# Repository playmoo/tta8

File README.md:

# tta8
8bit Transport Triggered Processor

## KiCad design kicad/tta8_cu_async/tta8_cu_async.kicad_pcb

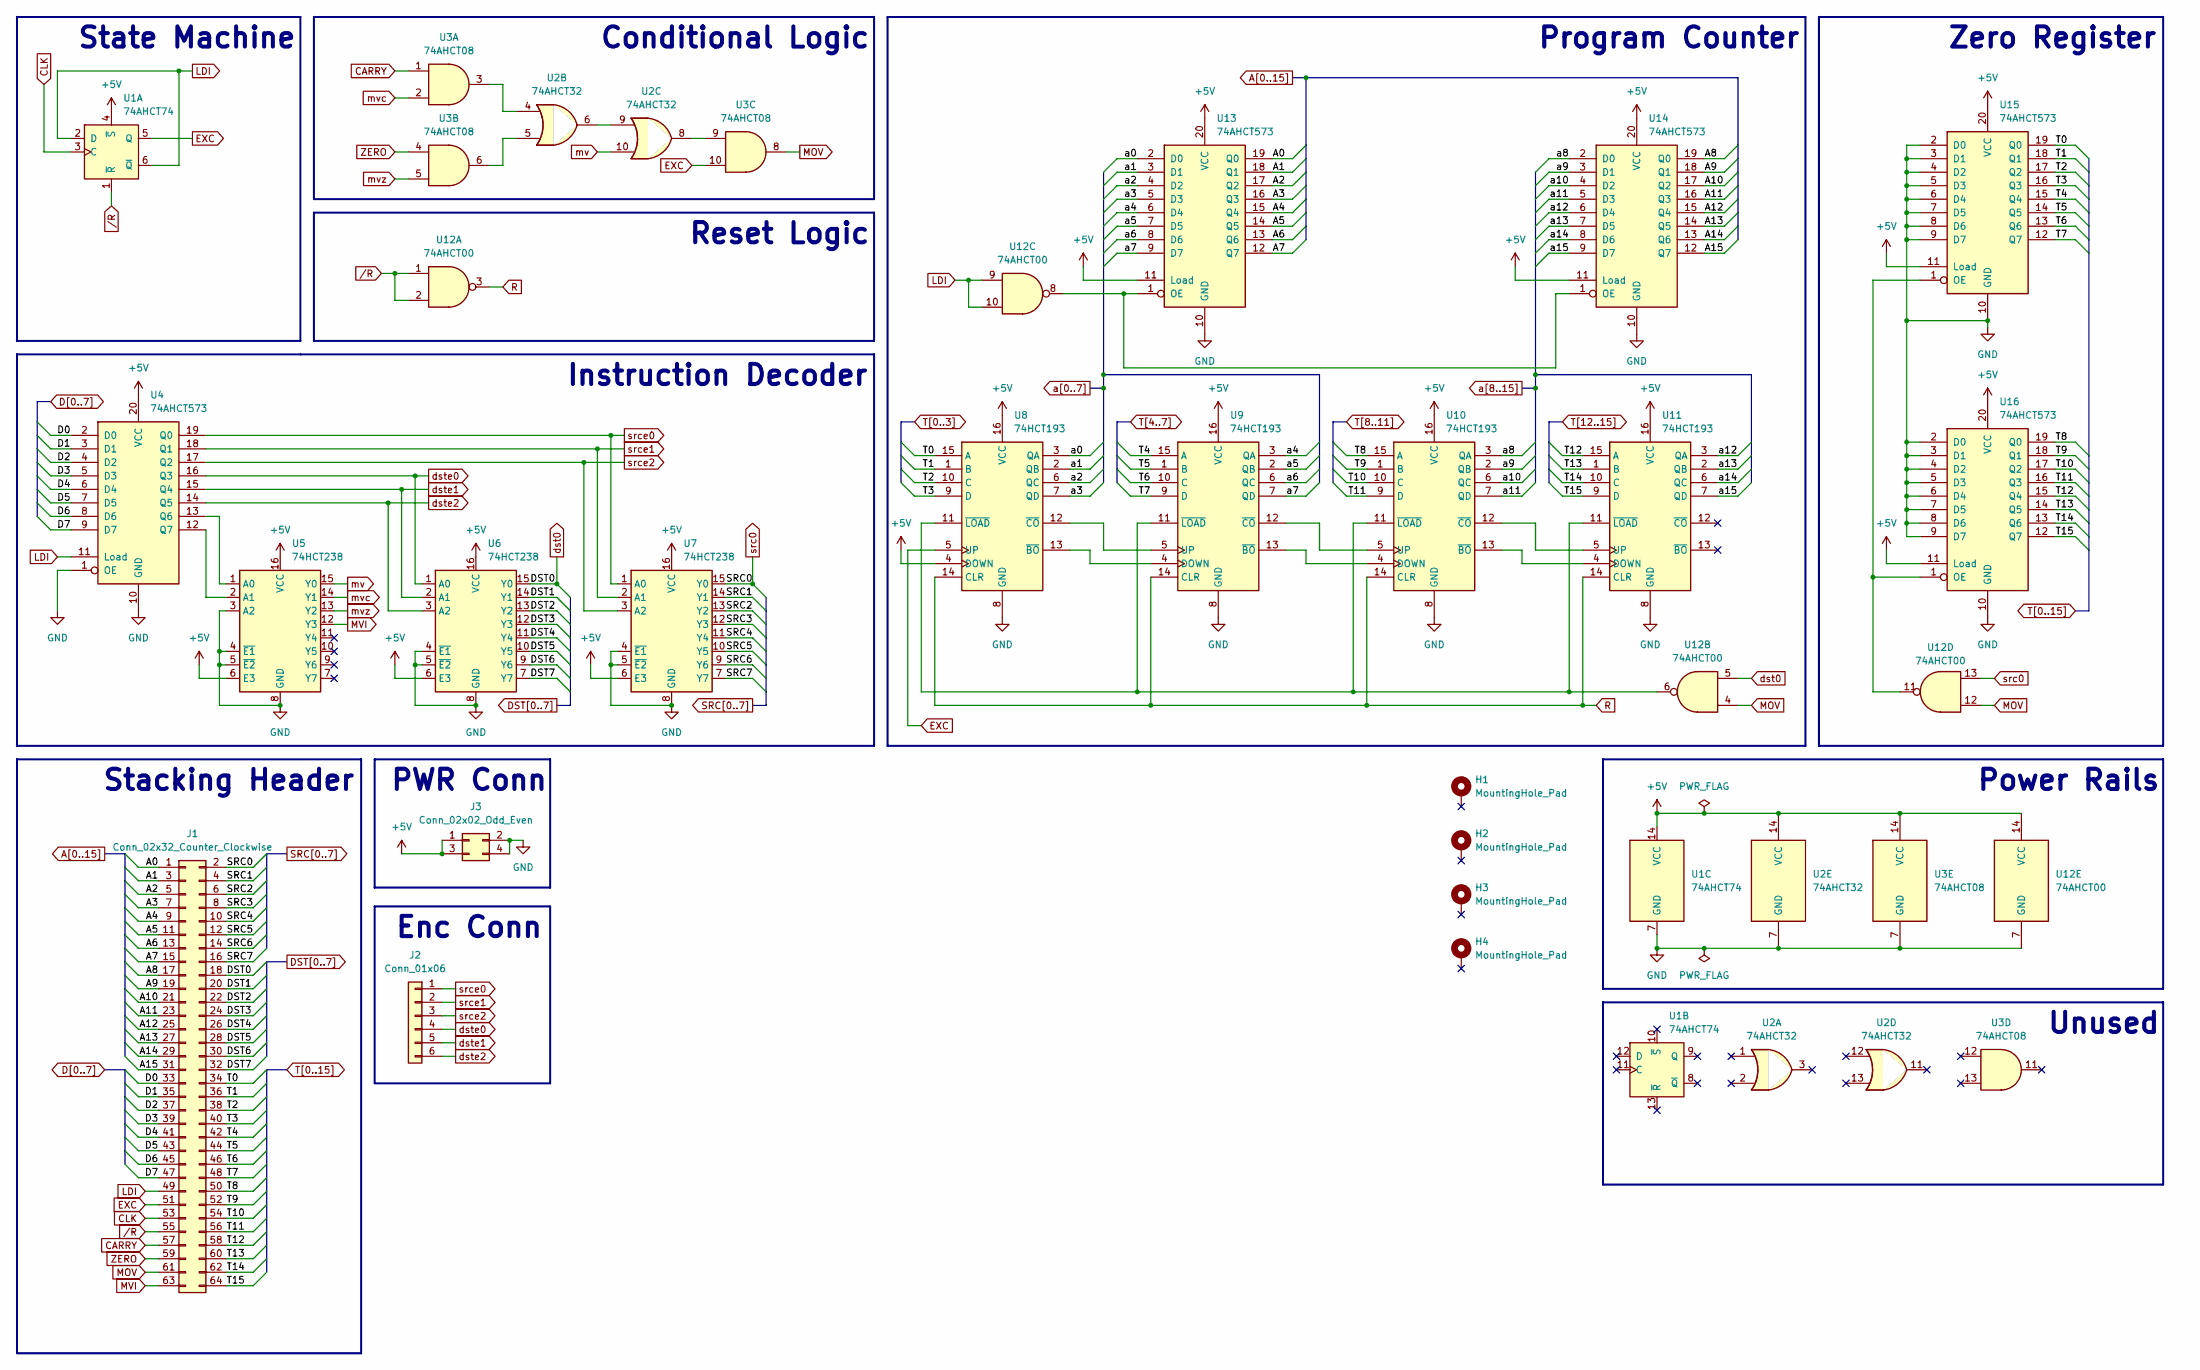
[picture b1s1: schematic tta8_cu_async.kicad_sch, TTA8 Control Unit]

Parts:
H1, H2, H3, H4: MountingHole_Pad; MountingHole_3.2mm_M3_Pad
J1: Conn_02x32_Counter_Clockwise; PinHeader_2x32_P2.54mm_Vertical
J2: Conn_01x06; PinSocket_1x06_P2.54mm_Vertical
J3: Conn_02x02_Odd_Even; Molex_Micro-Fit_3.0_43045-0400_2x02_P3.00mm_Horizontal
U1: 74AHCT74; DIP-14_W7.62mm_Socket
U2: 74AHCT32; DIP-14_W7.62mm_Socket
U3: 74AHCT08; DIP-14_W7.62mm_Socket
U4, U13, U14, U15, U16: 74AHCT573; DIP-20_W7.62mm_Socket
U5, U6, U7: 74HCT238; DIP-16_W7.62mm_Socket
U8, U9, U10, U11: 74HCT193; DIP-16_W7.62mm_Socket
U12: 74AHCT00; DIP-14_W7.62mm_Socket

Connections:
+5V: J3.1, J3.3, U1.4 (~S), U1.14 (VCC), U2.14 (VCC), U3.14 (VCC), U4.20 (VCC), U5.6 (E3), U5.16 (VCC), U6.6 (E3), U6.16 (VCC), U7.6 (E3), U7.16 (VCC), U8.4 (DOWN), U8.16 (VCC), U9.16 (VCC), U10.16 (VCC), U11.16 (VCC), U12.14 (VCC), U13.11 (Load), U13.20 (VCC), U14.11 (Load), U14.20 (VCC), U15.11 (Load), U15.20 (VCC), U16.11 (Load), U16.20 (VCC)
A0: J1.1, U13.19 (Q0)
A1: J1.3, U13.18 (Q1)
A2: J1.5, U13.17 (Q2)
A3: J1.7, U13.16 (Q3)
A4: J1.9, U13.15 (Q4)
A5: J1.11, U13.14 (Q5)
A6: J1.13, U13.13 (Q6)
A7: J1.15, U13.12 (Q7)
A8: J1.17, U14.19 (Q0)
A9: J1.19, U14.18 (Q1)
A10: J1.21, U14.17 (Q2)
A11: J1.23, U14.16 (Q3)
A12: J1.25, U14.15 (Q4)
A13: J1.27, U14.14 (Q5)
A14: J1.29, U14.13 (Q6)
A15: J1.31, U14.12 (Q7)
CARRY: J1.57, U3.1
CLK: J1.53, U1.3 (C)
D0: J1.33, U4.2 (D0)
D1: J1.35, U4.3 (D1)
D2: J1.37, U4.4 (D2)
D3: J1.39, U4.5 (D3)
D4: J1.41, U4.6 (D4)
D5: J1.43, U4.7 (D5)
D6: J1.45, U4.8 (D6)
D7: J1.47, U4.9 (D7)
DST1: J1.20, U6.14 (Y1)
DST2: J1.22, U6.13 (Y2)
DST3: J1.24, U6.12 (Y3)
DST4: J1.26, U6.11 (Y4)
DST5: J1.28, U6.10 (Y5)
DST6: J1.30, U6.9 (Y6)
DST7: J1.32, U6.7 (Y7)
EXC: J1.51, U1.5 (Q), U3.10, U8.5 (UP)
GND: J3.2, J3.4, U1.7 (GND), U2.7 (GND), U3.7 (GND), U4.1 (OE), U4.10 (GND), U5.3 (A2), U5.4 (~E1), U5.5 (~E2), U5.8 (GND), U6.4 (~E1), U6.5 (~E2), U6.8 (GND), U7.4 (~E1), U7.5 (~E2), U7.8 (GND), U8.8 (GND), U9.8 (GND), U10.8 (GND), U11.8 (GND), U12.7 (GND), U13.10 (GND), U14.10 (GND), U15.2 (D0), U15.3 (D1), U15.4 (D2), U15.5 (D3), U15.6 (D4), U15.7 (D5), U15.8 (D6), U15.9 (D7), U15.10 (GND), U16.2 (D0), U16.3 (D1), U16.4 (D2), U16.5 (D3), U16.6 (D4), U16.7 (D5), U16.8 (D6), U16.9 (D7), U16.10 (GND)
LDI: J1.49, U1.2 (D), U1.6 (~Q), U4.11 (Load), U12.9, U12.10
MOV: J1.61, U3.8, U12.4, U12.12
MVI: J1.63, U5.12 (Y3)
unnamed: U2.4, U3.3
unnamed: U2.5, U3.6
unnamed: U2.6, U2.9
unnamed: U2.8, U3.9
unnamed: U4.13 (Q6), U5.1 (A0)
unnamed: U4.12 (Q7), U5.2 (A1)
unnamed: U8.13 (~BO), U9.4 (DOWN)
unnamed: U8.12 (~CO), U9.5 (UP)
unnamed: U9.13 (~BO), U10.4 (DOWN)
unnamed: U9.12 (~CO), U10.5 (UP)
unnamed: U10.13 (~BO), U11.4 (DOWN)
unnamed: U10.12 (~CO), U11.5 (UP)
unnamed: U8.11 (~LOAD), U9.11 (~LOAD), U10.11 (~LOAD), U11.11 (~LOAD), U12.6
unnamed: U12.8, U13.1 (OE), U14.1 (OE)
unnamed: U12.11, U15.1 (OE), U16.1 (OE)
R: U8.14 (CLR), U9.14 (CLR), U10.14 (CLR), U11.14 (CLR), U12.3
SRC1: J1.4, U7.14 (Y1)
SRC2: J1.6, U7.13 (Y2)
SRC3: J1.8, U7.12 (Y3)
SRC4: J1.10, U7.11 (Y4)
SRC5: J1.12, U7.10 (Y5)
SRC6: J1.14, U7.9 (Y6)
SRC7: J1.16, U7.7 (Y7)
T0: J1.34, U8.15 (A), U15.19 (Q0)
T1: J1.36, U8.1 (B), U15.18 (Q1)
T2: J1.38, U8.10 (C), U15.17 (Q2)
T3: J1.40, U8.9 (D), U15.16 (Q3)
T4: J1.42, U9.15 (A), U15.15 (Q4)
T5: J1.44, U9.1 (B), U15.14 (Q5)
T6: J1.46, U9.10 (C), U15.13 (Q6)
T7: J1.48, U9.9 (D), U15.12 (Q7)
T8: J1.50, U10.15 (A), U16.19 (Q0)
T9: J1.52, U10.1 (B), U16.18 (Q1)
T10: J1.54, U10.10 (C), U16.17 (Q2)
T11: J1.56, U10.9 (D), U16.16 (Q3)
T12: J1.58, U11.15 (A), U16.15 (Q4)
T13: J1.60, U11.1 (B), U16.14 (Q5)
T14: J1.62, U11.10 (C), U16.13 (Q6)
T15: J1.64, U11.9 (D), U16.12 (Q7)
ZERO: J1.59, U3.4
a0: U8.3 (QA), U13.2 (D0)
a1: U8.2 (QB), U13.3 (D1)
a2: U8.6 (QC), U13.4 (D2)
a3: U8.7 (QD), U13.5 (D3)
a4: U9.3 (QA), U13.6 (D4)
a5: U9.2 (QB), U13.7 (D5)
a6: U9.6 (QC), U13.8 (D6)
a7: U9.7 (QD), U13.9 (D7)
a8: U10.3 (QA), U14.2 (D0)
a9: U10.2 (QB), U14.3 (D1)
a10: U10.6 (QC), U14.4 (D2)
a11: U10.7 (QD), U14.5 (D3)
a12: U11.3 (QA), U14.6 (D4)
a13: U11.2 (QB), U14.7 (D5)
a14: U11.6 (QC), U14.8 (D6)
a15: U11.7 (QD), U14.9 (D7)
dst0: J1.18, U6.15 (Y0), U12.5
dste0: J2.4, U4.16 (Q3), U6.1 (A0)
dste1: J2.5, U4.15 (Q4), U6.2 (A1)
dste2: J2.6, U4.14 (Q5), U6.3 (A2)
mv: U2.10, U5.15 (Y0)
mvc: U3.2, U5.14 (Y1)
mvz: U3.5, U5.13 (Y2)
src0: J1.2, U7.15 (Y0), U12.13
srce0: J2.1, U4.19 (Q0), U7.1 (A0)
srce1: J2.2, U4.18 (Q1), U7.2 (A1)
srce2: J2.3, U4.17 (Q2), U7.3 (A2)
/R: J1.55, U1.1 (~R), U12.1, U12.2

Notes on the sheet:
Conditional Logic
PWR Conn
Unused
Reset Logic
Enc Conn
State Machine
Instruction Decoder
Program Counter
Stacking Header
Power Rails
Zero Register

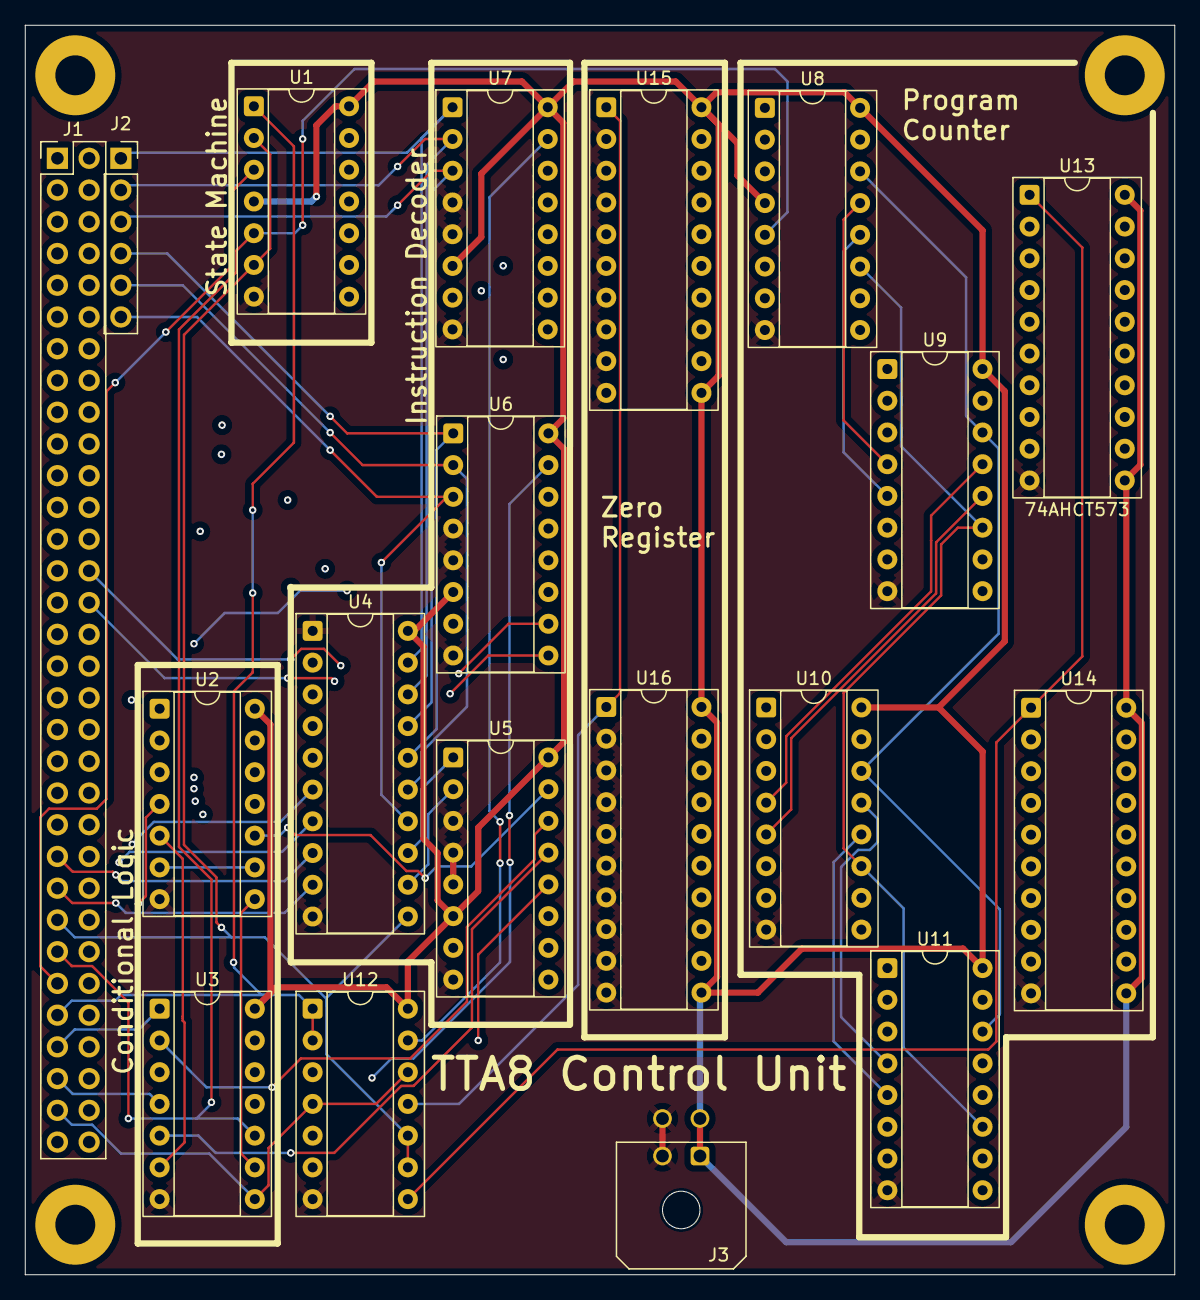
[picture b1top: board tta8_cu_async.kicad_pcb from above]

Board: 4 copper layers, 92.0 x 100.0 mm, 23 parts (0 on the bottom side), 107 nets.

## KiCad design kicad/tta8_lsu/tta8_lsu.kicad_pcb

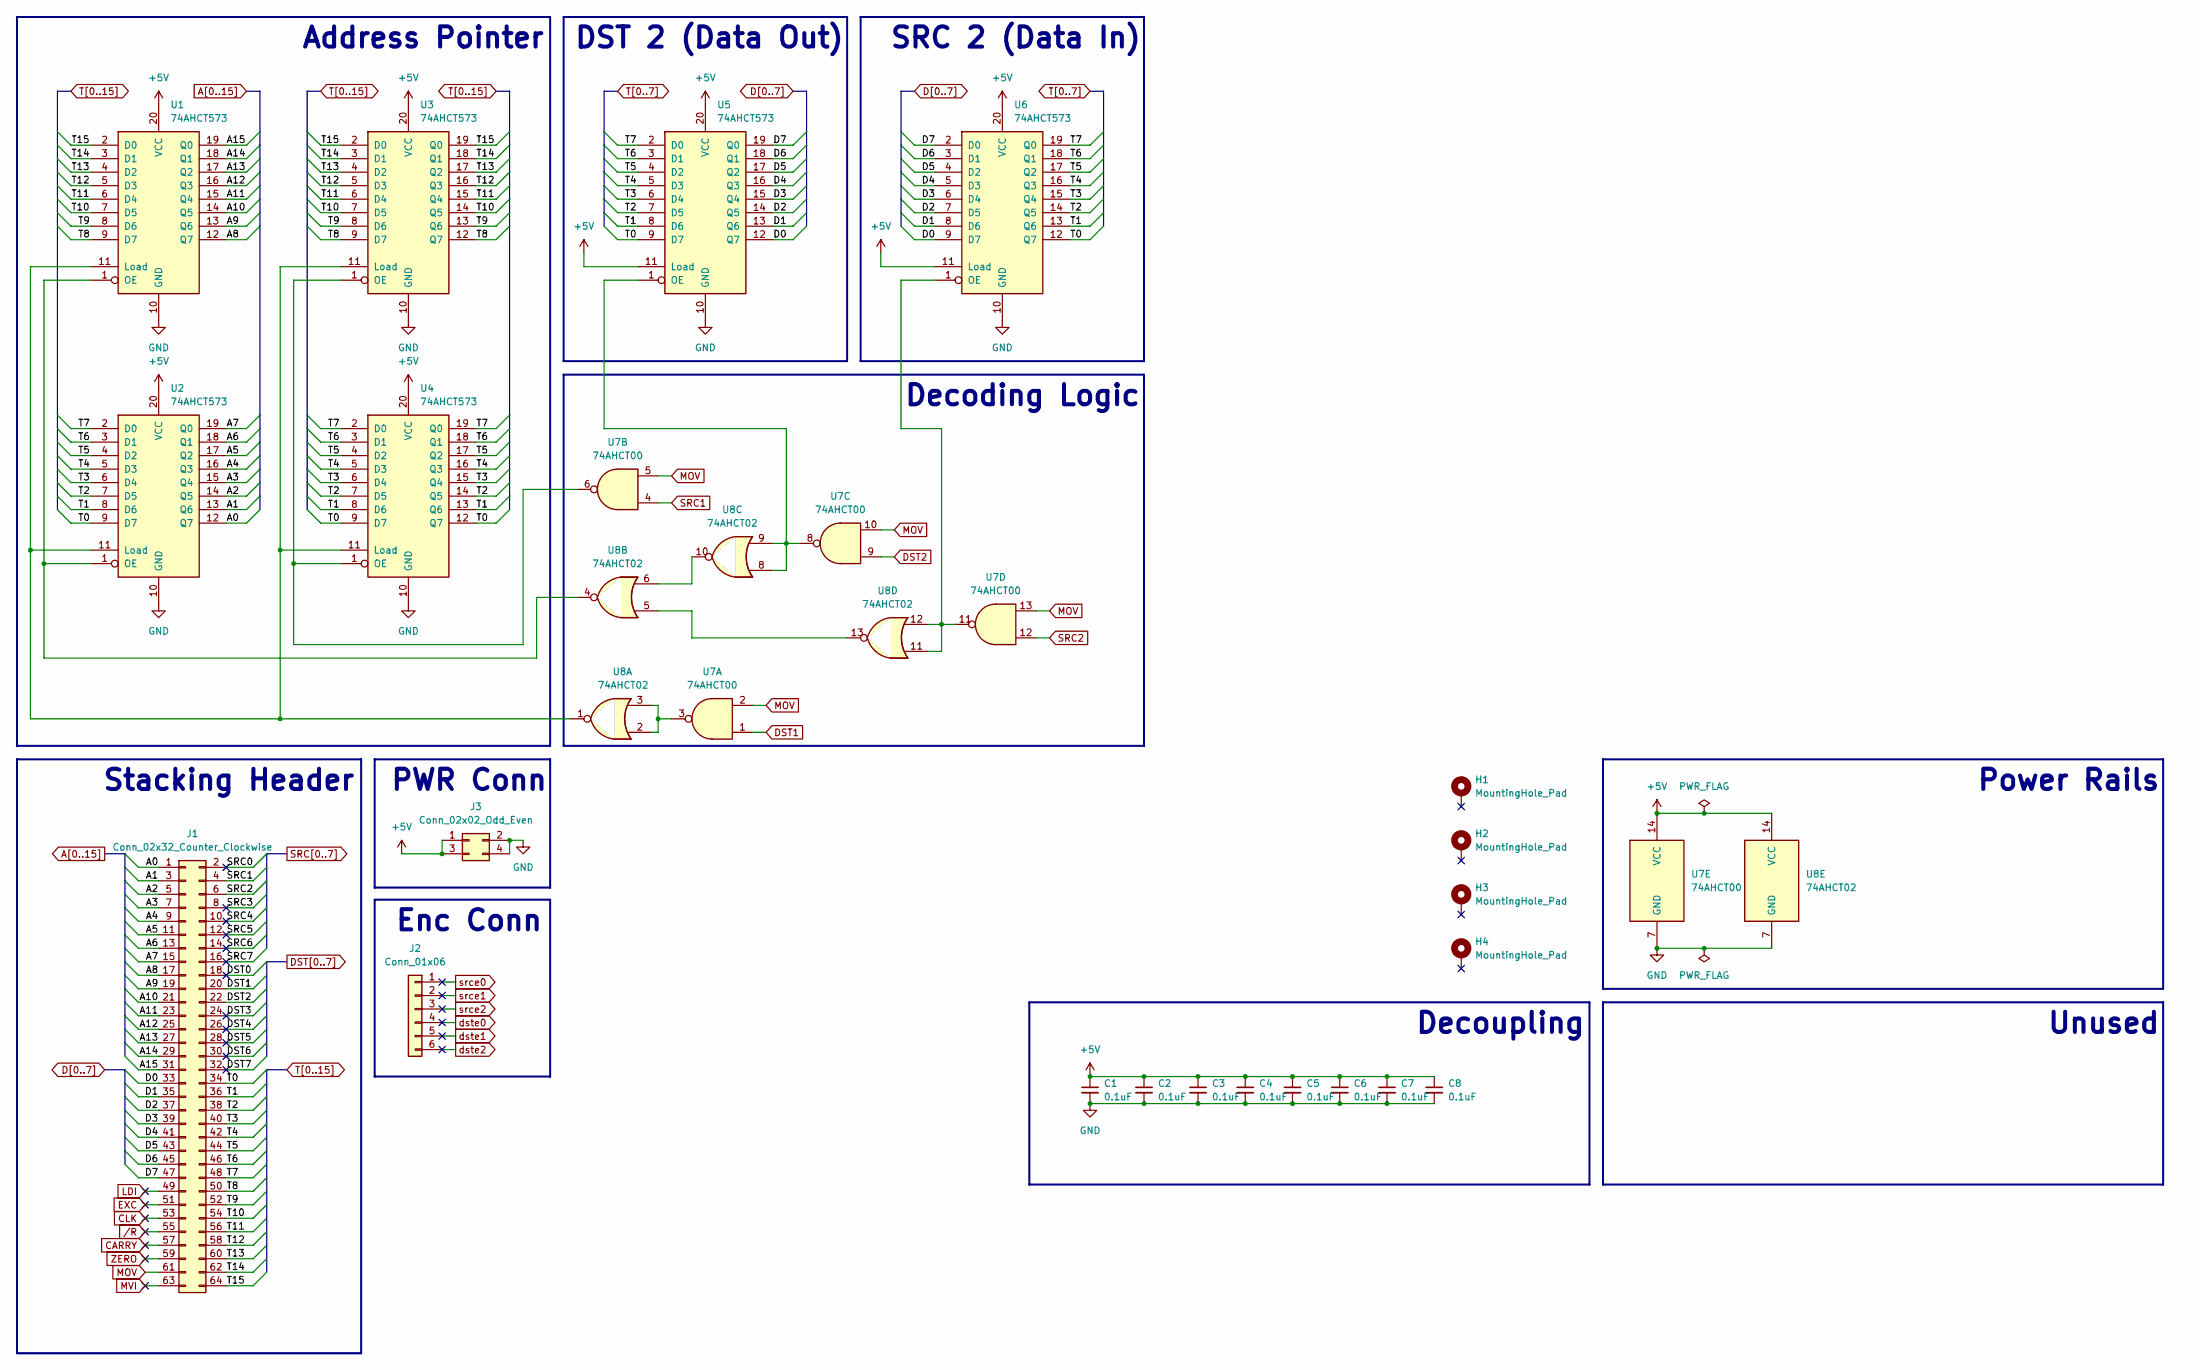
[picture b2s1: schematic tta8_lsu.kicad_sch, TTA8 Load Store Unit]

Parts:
C1, C2, C3, C4, C5, C6, C7, C8: 0.1uF; C_Disc_D5.0mm_W2.5mm_P2.50mm
H1, H2, H3, H4: MountingHole_Pad; MountingHole_3.2mm_M3_Pad
J1: Conn_02x32_Counter_Clockwise; PinHeader_2x32_P2.54mm_Vertical
J2: Conn_01x06; PinSocket_1x06_P2.54mm_Vertical
J3: Conn_02x02_Odd_Even; Molex_Micro-Fit_3.0_43045-0400_2x02_P3.00mm_Horizontal
U1, U2, U3, U4, U5, U6: 74AHCT573; DIP-20_W7.62mm
U7: 74AHCT00; DIP-14_W7.62mm
U8: 74AHCT02; DIP-14_W7.62mm

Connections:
+5V: C1.1, C2.1, C3.1, C4.1, C5.1, C6.1, C7.1, C8.1, J3.1, J3.3, U1.20 (VCC), U2.20 (VCC), U3.20 (VCC), U4.20 (VCC), U5.11 (Load), U5.20 (VCC), U6.11 (Load), U6.20 (VCC), U7.14 (VCC), U8.14 (VCC)
A0: J1.1, U2.12 (Q7)
A1: J1.3, U2.13 (Q6)
A2: J1.5, U2.14 (Q5)
A3: J1.7, U2.15 (Q4)
A4: J1.9, U2.16 (Q3)
A5: J1.11, U2.17 (Q2)
A6: J1.13, U2.18 (Q1)
A7: J1.15, U2.19 (Q0)
A8: J1.17, U1.12 (Q7)
A9: J1.19, U1.13 (Q6)
A10: J1.21, U1.14 (Q5)
A11: J1.23, U1.15 (Q4)
A12: J1.25, U1.16 (Q3)
A13: J1.27, U1.17 (Q2)
A14: J1.29, U1.18 (Q1)
A15: J1.31, U1.19 (Q0)
CARRY: J1.57
CLK: J1.53
D0: J1.33, U5.12 (Q7), U6.9 (D7)
D1: J1.35, U5.13 (Q6), U6.8 (D6)
D2: J1.37, U5.14 (Q5), U6.7 (D5)
D3: J1.39, U5.15 (Q4), U6.6 (D4)
D4: J1.41, U5.16 (Q3), U6.5 (D3)
D5: J1.43, U5.17 (Q2), U6.4 (D2)
D6: J1.45, U5.18 (Q1), U6.3 (D1)
D7: J1.47, U5.19 (Q0), U6.2 (D0)
DST0: J1.18
DST1: J1.20, U7.1
DST2: J1.22, U7.9
DST3: J1.24
DST4: J1.26
DST5: J1.28
DST6: J1.30
DST7: J1.32
EXC: J1.51
GND: C1.2, C2.2, C3.2, C4.2, C5.2, C6.2, C7.2, C8.2, J3.2, J3.4, U1.10 (GND), U2.10 (GND), U3.10 (GND), U4.10 (GND), U5.10 (GND), U6.10 (GND), U7.7 (GND), U8.7 (GND)
LDI: J1.49
MOV: J1.61, U7.2, U7.5, U7.10, U7.13
MVI: J1.63
unnamed: U1.11 (Load), U2.11 (Load), U3.11 (Load), U4.11 (Load), U8.1
unnamed: U1.1 (OE), U2.1 (OE), U8.4
unnamed: U3.1 (OE), U4.1 (OE), U7.6
unnamed: U5.1 (OE), U7.8, U8.8, U8.9
unnamed: U6.1 (OE), U7.11, U8.11, U8.12
unnamed: U7.3, U8.2, U8.3
unnamed: U8.6, U8.10
unnamed: U8.5, U8.13
SRC0: J1.2
SRC1: J1.4, U7.4
SRC2: J1.6, U7.12
SRC3: J1.8
SRC4: J1.10
SRC5: J1.12
SRC6: J1.14
SRC7: J1.16
T0: J1.34, U2.9 (D7), U4.9 (D7), U4.12 (Q7), U5.9 (D7), U6.12 (Q7)
T1: J1.36, U2.8 (D6), U4.8 (D6), U4.13 (Q6), U5.8 (D6), U6.13 (Q6)
T2: J1.38, U2.7 (D5), U4.7 (D5), U4.14 (Q5), U5.7 (D5), U6.14 (Q5)
T3: J1.40, U2.6 (D4), U4.6 (D4), U4.15 (Q4), U5.6 (D4), U6.15 (Q4)
T4: J1.42, U2.5 (D3), U4.5 (D3), U4.16 (Q3), U5.5 (D3), U6.16 (Q3)
T5: J1.44, U2.4 (D2), U4.4 (D2), U4.17 (Q2), U5.4 (D2), U6.17 (Q2)
T6: J1.46, U2.3 (D1), U4.3 (D1), U4.18 (Q1), U5.3 (D1), U6.18 (Q1)
T7: J1.48, U2.2 (D0), U4.2 (D0), U4.19 (Q0), U5.2 (D0), U6.19 (Q0)
T8: J1.50, U1.9 (D7), U3.9 (D7), U3.12 (Q7)
T9: J1.52, U1.8 (D6), U3.8 (D6), U3.13 (Q6)
T10: J1.54, U1.7 (D5), U3.7 (D5), U3.14 (Q5)
T11: J1.56, U1.6 (D4), U3.6 (D4), U3.15 (Q4)
T12: J1.58, U1.5 (D3), U3.5 (D3), U3.16 (Q3)
T13: J1.60, U1.4 (D2), U3.4 (D2), U3.17 (Q2)
T14: J1.62, U1.3 (D1), U3.3 (D1), U3.18 (Q1)
T15: J1.64, U1.2 (D0), U3.2 (D0), U3.19 (Q0)
ZERO: J1.59
dste0: J2.4
dste1: J2.5
dste2: J2.6
srce0: J2.1
srce1: J2.2
srce2: J2.3
/R: J1.55

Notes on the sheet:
Decoding Logic
Decoupling
PWR Conn
Unused
Enc Conn
Address Pointer
DST 2 (Data Out)
Stacking Header
Power Rails
SRC 2 (Data In)

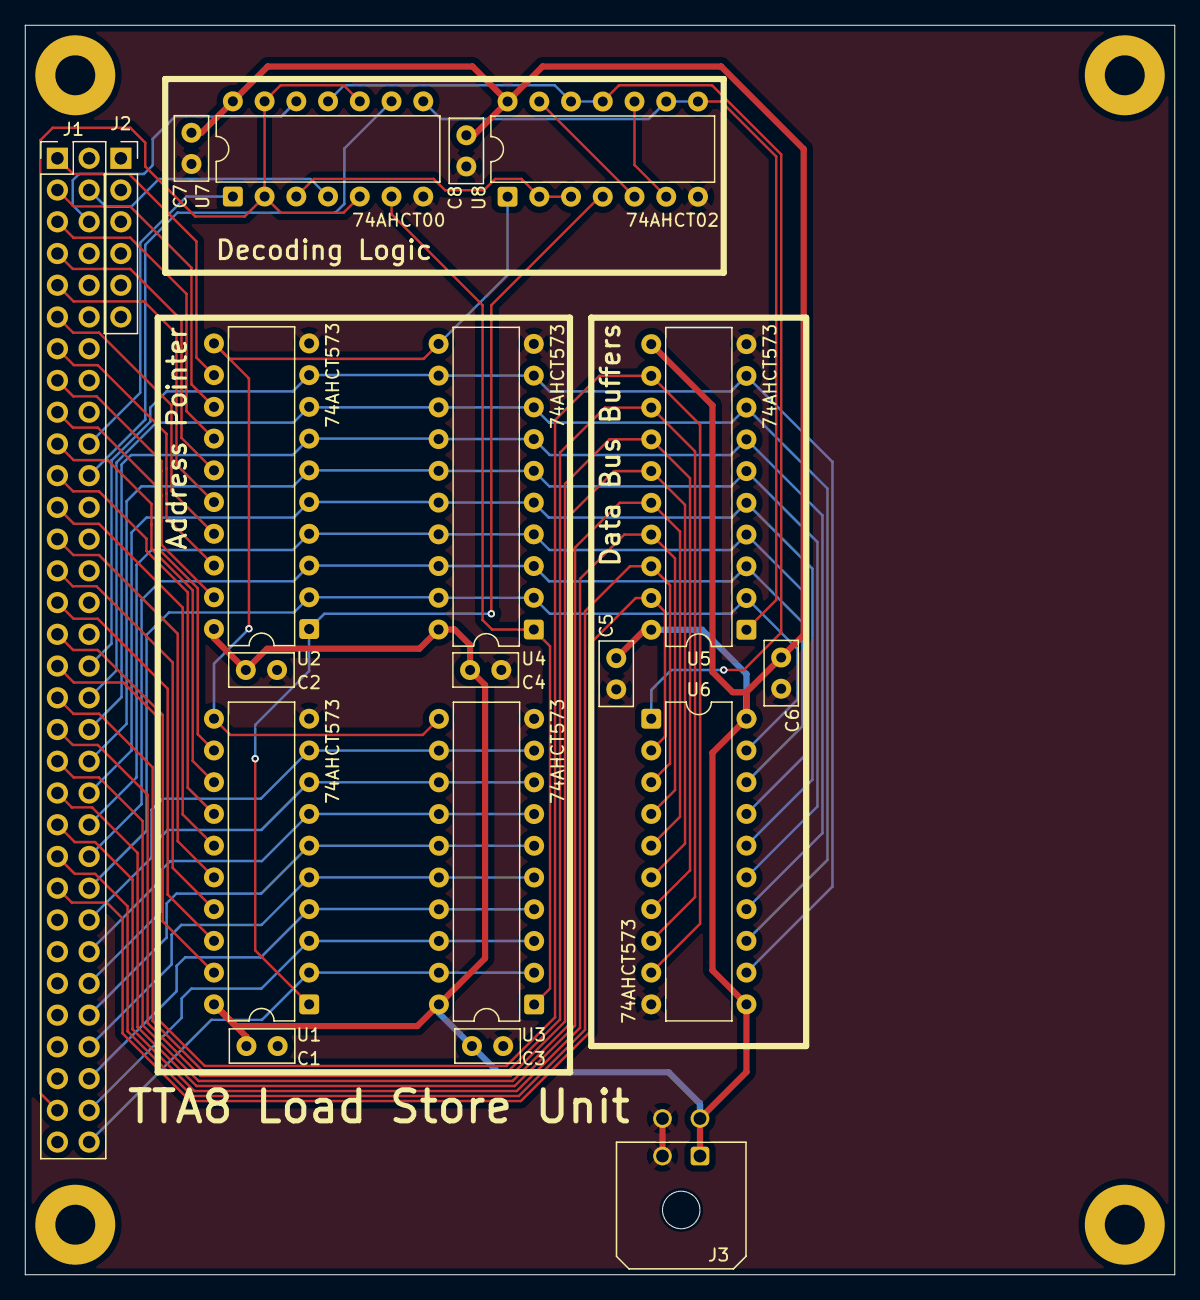
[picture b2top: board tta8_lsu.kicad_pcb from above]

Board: 2 copper layers, 92.0 x 100.0 mm, 23 parts (0 on the bottom side), 55 nets.

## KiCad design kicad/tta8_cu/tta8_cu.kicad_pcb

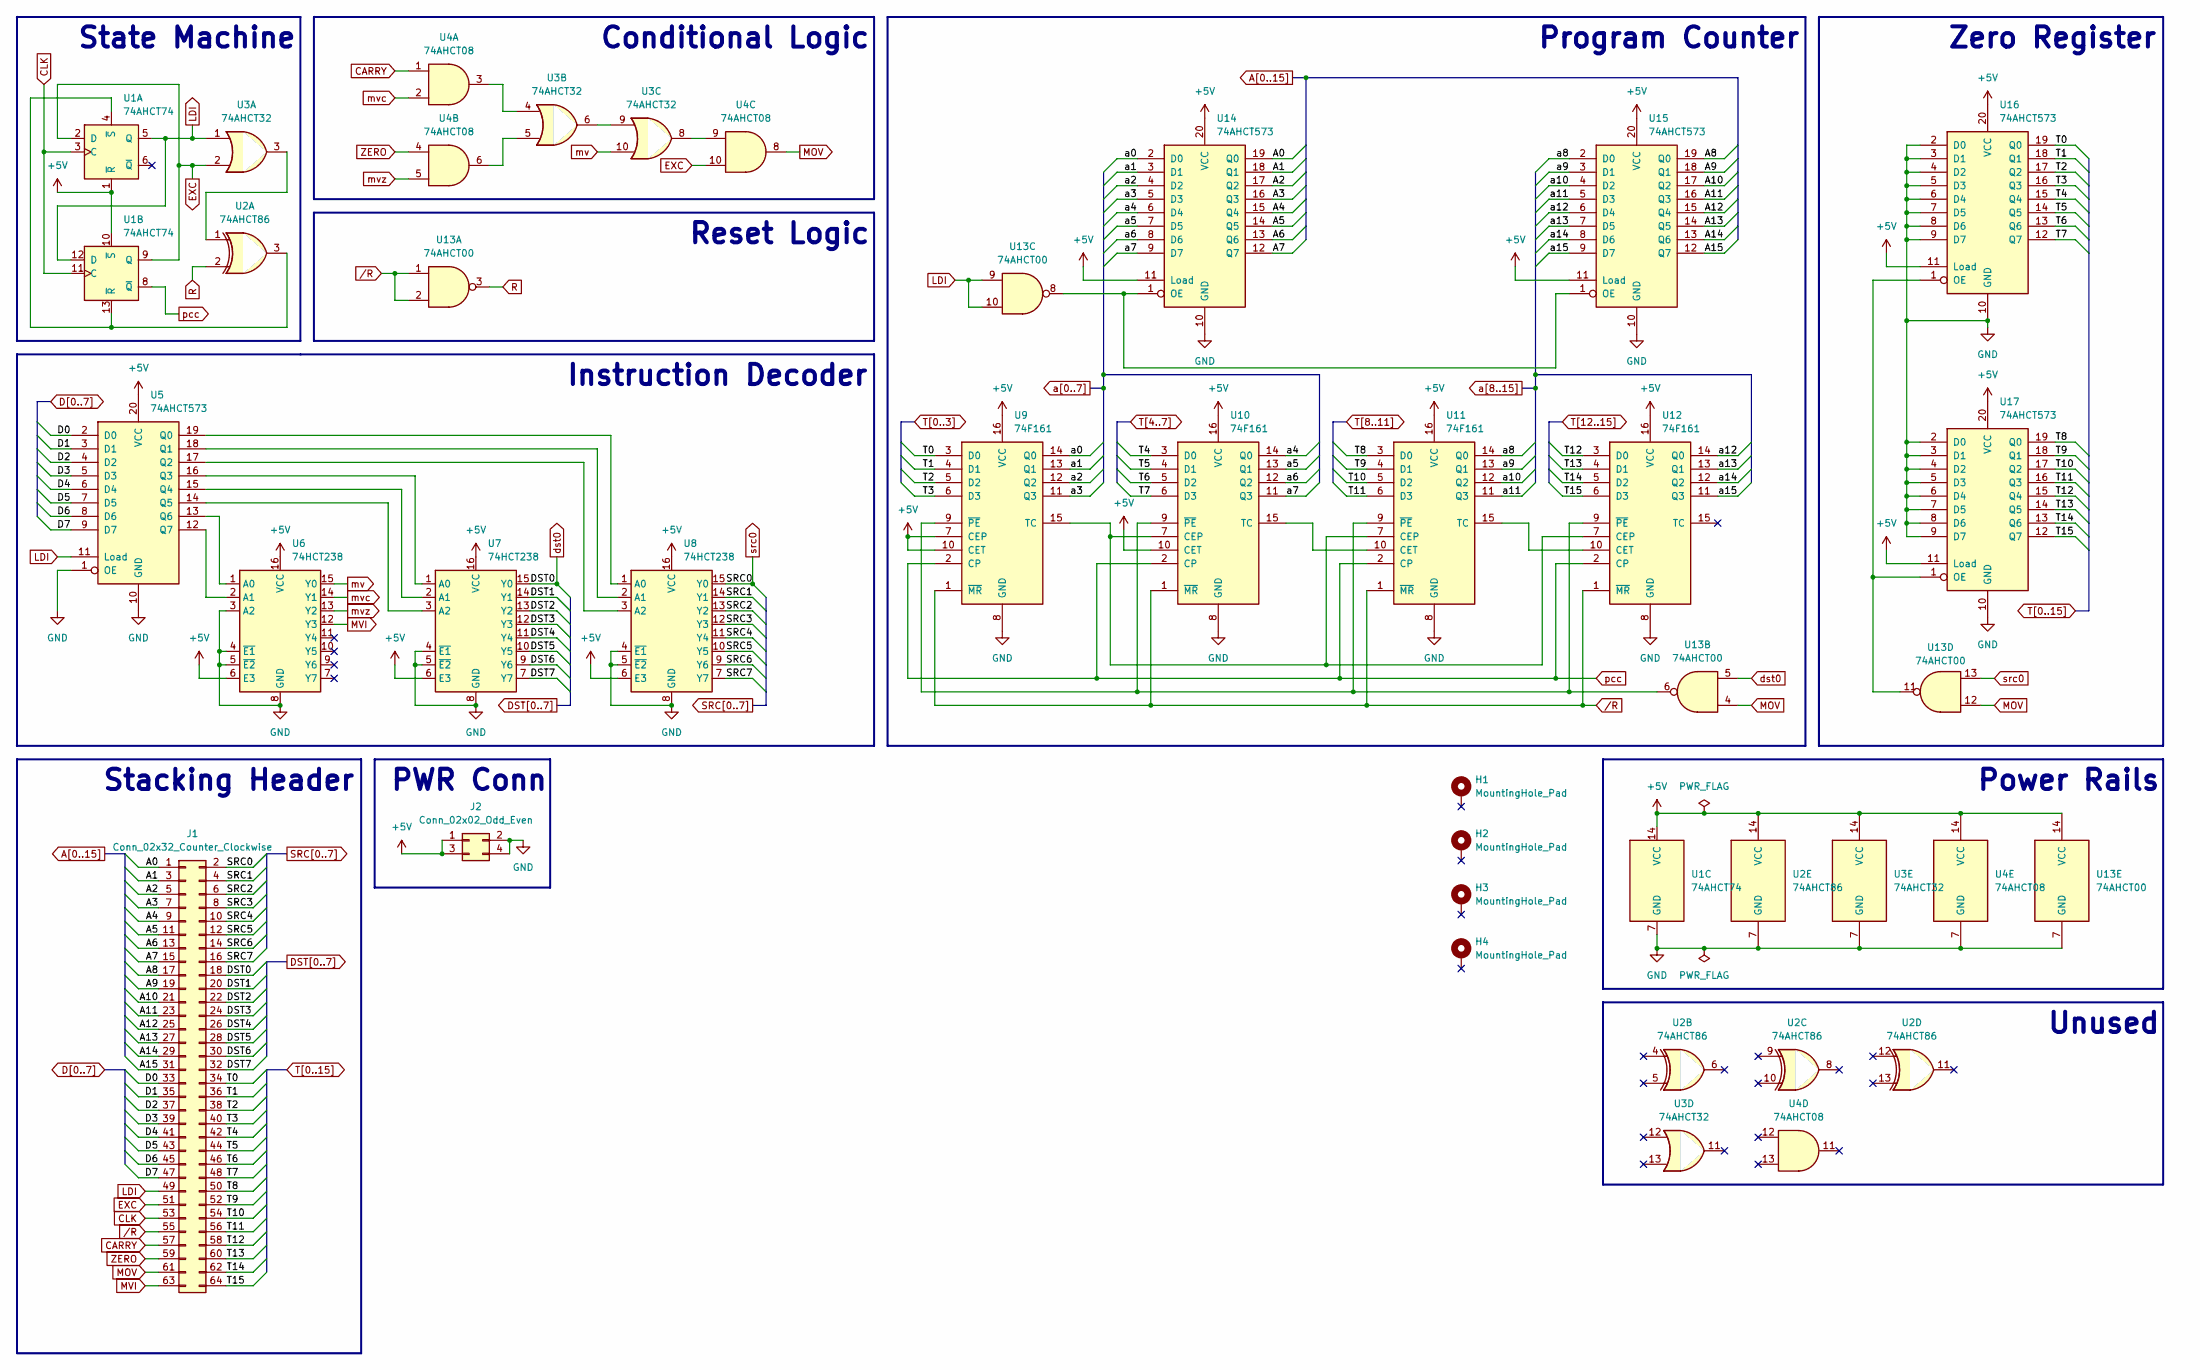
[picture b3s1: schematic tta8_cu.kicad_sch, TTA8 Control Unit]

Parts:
H1, H2, H3, H4: MountingHole_Pad; MountingHole_3.2mm_M3_Pad
J1: Conn_02x32_Counter_Clockwise; PinHeader_2x32_P2.54mm_Vertical
J2: Conn_02x02_Odd_Even; Molex_Micro-Fit_3.0_43045-0400_2x02_P3.00mm_Horizontal
U1: 74AHCT74; DIP-14_W7.62mm
U2: 74AHCT86; DIP-14_W7.62mm
U3: 74AHCT32; DIP-14_W7.62mm
U4: 74AHCT08; DIP-14_W7.62mm
U5, U14, U15, U16, U17: 74AHCT573; DIP-20_W7.62mm
U6, U7, U8: 74HCT238; DIP-16_W7.62mm
U9, U10, U11, U12: 74F161; DIP-16_W7.62mm
U13: 74AHCT00; DIP-14_W7.62mm

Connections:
+5V: J2.1, J2.3, U1.1 (~R), U1.10 (~S), U1.14 (VCC), U2.14 (VCC), U3.14 (VCC), U4.14 (VCC), U5.20 (VCC), U6.6 (E3), U6.16 (VCC), U7.6 (E3), U7.16 (VCC), U8.6 (E3), U8.16 (VCC), U9.7 (CEP), U9.10 (CET), U9.16 (VCC), U10.10 (CET), U10.16 (VCC), U11.16 (VCC), U12.16 (VCC), U13.14 (VCC), U14.11 (Load), U14.20 (VCC), U15.11 (Load), U15.20 (VCC), U16.11 (Load), U16.20 (VCC), U17.11 (Load), U17.20 (VCC)
A0: J1.1, U14.19 (Q0)
A1: J1.3, U14.18 (Q1)
A2: J1.5, U14.17 (Q2)
A3: J1.7, U14.16 (Q3)
A4: J1.9, U14.15 (Q4)
A5: J1.11, U14.14 (Q5)
A6: J1.13, U14.13 (Q6)
A7: J1.15, U14.12 (Q7)
A8: J1.17, U15.19 (Q0)
A9: J1.19, U15.18 (Q1)
A10: J1.21, U15.17 (Q2)
A11: J1.23, U15.16 (Q3)
A12: J1.25, U15.15 (Q4)
A13: J1.27, U15.14 (Q5)
A14: J1.29, U15.13 (Q6)
A15: J1.31, U15.12 (Q7)
CARRY: J1.57, U4.1
CLK: J1.53, U1.3 (C), U1.11 (C)
D0: J1.33, U5.2 (D0)
D1: J1.35, U5.3 (D1)
D2: J1.37, U5.4 (D2)
D3: J1.39, U5.5 (D3)
D4: J1.41, U5.6 (D4)
D5: J1.43, U5.7 (D5)
D6: J1.45, U5.8 (D6)
D7: J1.47, U5.9 (D7)
DST1: J1.20, U7.14 (Y1)
DST2: J1.22, U7.13 (Y2)
DST3: J1.24, U7.12 (Y3)
DST4: J1.26, U7.11 (Y4)
DST5: J1.28, U7.10 (Y5)
DST6: J1.30, U7.9 (Y6)
DST7: J1.32, U7.7 (Y7)
EXC: J1.51, U1.2 (D), U1.9 (Q), U3.2, U4.10
GND: J2.2, J2.4, U1.7 (GND), U2.7 (GND), U3.7 (GND), U4.7 (GND), U5.1 (OE), U5.10 (GND), U6.3 (A2), U6.4 (~E1), U6.5 (~E2), U6.8 (GND), U7.4 (~E1), U7.5 (~E2), U7.8 (GND), U8.4 (~E1), U8.5 (~E2), U8.8 (GND), U9.8 (GND), U10.8 (GND), U11.8 (GND), U12.8 (GND), U13.7 (GND), U14.10 (GND), U15.10 (GND), U16.2 (D0), U16.3 (D1), U16.4 (D2), U16.5 (D3), U16.6 (D4), U16.7 (D5), U16.8 (D6), U16.9 (D7), U16.10 (GND), U17.2 (D0), U17.3 (D1), U17.4 (D2), U17.5 (D3), U17.6 (D4), U17.7 (D5), U17.8 (D6), U17.9 (D7), U17.10 (GND)
LDI: J1.49, U1.5 (Q), U1.12 (D), U3.1, U5.11 (Load), U13.9, U13.10
MOV: J1.61, U4.8, U13.4, U13.12
MVI: J1.63, U6.12 (Y3)
unnamed: U1.4 (~S), U1.13 (~R), U2.3
unnamed: U2.1, U3.3
unnamed: U3.4, U4.3
unnamed: U3.5, U4.6
unnamed: U3.6, U3.9
unnamed: U3.8, U4.9
unnamed: U5.19 (Q0), U8.1 (A0)
unnamed: U5.18 (Q1), U8.2 (A1)
unnamed: U5.17 (Q2), U8.3 (A2)
unnamed: U5.16 (Q3), U7.1 (A0)
unnamed: U5.15 (Q4), U7.2 (A1)
unnamed: U5.14 (Q5), U7.3 (A2)
unnamed: U5.13 (Q6), U6.1 (A0)
unnamed: U5.12 (Q7), U6.2 (A1)
unnamed: U9.15 (TC), U10.7 (CEP), U11.7 (CEP), U12.7 (CEP)
unnamed: U10.15 (TC), U11.10 (CET)
unnamed: U9.9 (~PE), U10.9 (~PE), U11.9 (~PE), U12.9 (~PE), U13.6
unnamed: U11.15 (TC), U12.10 (CET)
unnamed: U13.8, U14.1 (OE), U15.1 (OE)
unnamed: U13.11, U16.1 (OE), U17.1 (OE)
R: U2.2, U13.3
SRC1: J1.4, U8.14 (Y1)
SRC2: J1.6, U8.13 (Y2)
SRC3: J1.8, U8.12 (Y3)
SRC4: J1.10, U8.11 (Y4)
SRC5: J1.12, U8.10 (Y5)
SRC6: J1.14, U8.9 (Y6)
SRC7: J1.16, U8.7 (Y7)
T0: J1.34, U9.3 (D0), U16.19 (Q0)
T1: J1.36, U9.4 (D1), U16.18 (Q1)
T2: J1.38, U9.5 (D2), U16.17 (Q2)
T3: J1.40, U9.6 (D3), U16.16 (Q3)
T4: J1.42, U10.3 (D0), U16.15 (Q4)
T5: J1.44, U10.4 (D1), U16.14 (Q5)
T6: J1.46, U10.5 (D2), U16.13 (Q6)
T7: J1.48, U10.6 (D3), U16.12 (Q7)
T8: J1.50, U11.3 (D0), U17.19 (Q0)
T9: J1.52, U11.4 (D1), U17.18 (Q1)
T10: J1.54, U11.5 (D2), U17.17 (Q2)
T11: J1.56, U11.6 (D3), U17.16 (Q3)
T12: J1.58, U12.3 (D0), U17.15 (Q4)
T13: J1.60, U12.4 (D1), U17.14 (Q5)
T14: J1.62, U12.5 (D2), U17.13 (Q6)
T15: J1.64, U12.6 (D3), U17.12 (Q7)
ZERO: J1.59, U4.4
a0: U9.14 (Q0), U14.2 (D0)
a1: U9.13 (Q1), U14.3 (D1)
a2: U9.12 (Q2), U14.4 (D2)
a3: U9.11 (Q3), U14.5 (D3)
a4: U10.14 (Q0), U14.6 (D4)
a5: U10.13 (Q1), U14.7 (D5)
a6: U10.12 (Q2), U14.8 (D6)
a7: U10.11 (Q3), U14.9 (D7)
a8: U11.14 (Q0), U15.2 (D0)
a9: U11.13 (Q1), U15.3 (D1)
a10: U11.12 (Q2), U15.4 (D2)
a11: U11.11 (Q3), U15.5 (D3)
a12: U12.14 (Q0), U15.6 (D4)
a13: U12.13 (Q1), U15.7 (D5)
a14: U12.12 (Q2), U15.8 (D6)
a15: U12.11 (Q3), U15.9 (D7)
dst0: J1.18, U7.15 (Y0), U13.5
mv: U3.10, U6.15 (Y0)
mvc: U4.2, U6.14 (Y1)
mvz: U4.5, U6.13 (Y2)
pcc: U1.8 (~Q), U9.2 (CP), U10.2 (CP), U11.2 (CP), U12.2 (CP)
src0: J1.2, U8.15 (Y0), U13.13
/R: J1.55, U9.1 (~MR), U10.1 (~MR), U11.1 (~MR), U12.1 (~MR), U13.1, U13.2

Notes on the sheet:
Conditional Logic
PWR Conn
Unused
Reset Logic
State Machine
Instruction Decoder
Program Counter
Stacking Header
Power Rails
Zero Register

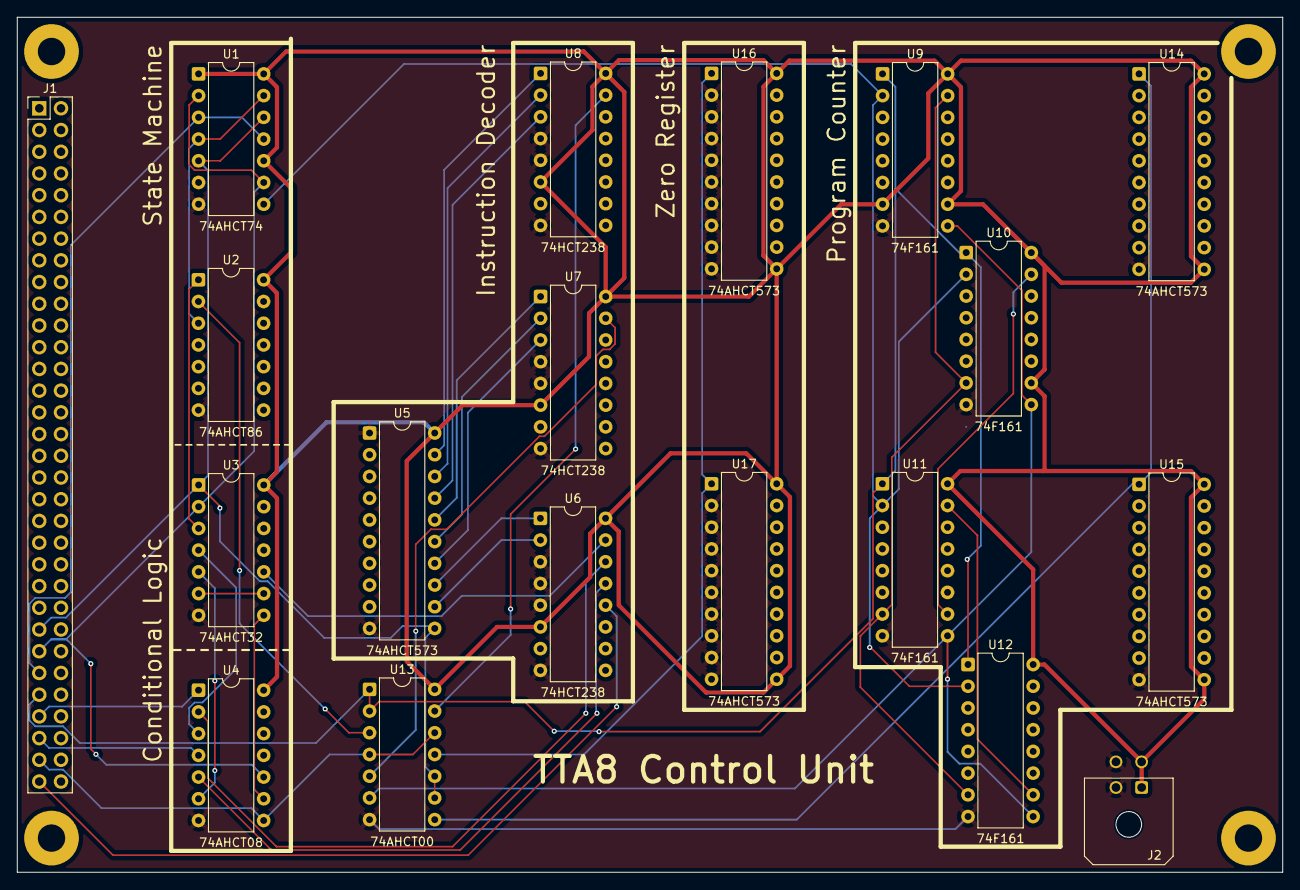
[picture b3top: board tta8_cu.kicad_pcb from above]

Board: 4 copper layers, 148.0 x 100.0 mm, 23 parts (0 on the bottom side), 107 nets.

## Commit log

2025-09-16 Remove old CU versions
2025-09-16 add LICENSE
    CERN OHL v2 Weakly Reciprocal
2025-09-17 remove backups
2025-09-17 Initial load store unit
2025-09-17 Ground fill changes + gerber zip
2025-09-17 Fix second address pointer register
    Was T->A supposed to be T->T
2025-09-22 Fix floating /S in State Machine
2025-09-22 Add decoupling to tt8 lsu
2025-10-01 cu change to sockets
2025-10-02 added pullup to high byte of t_bus
